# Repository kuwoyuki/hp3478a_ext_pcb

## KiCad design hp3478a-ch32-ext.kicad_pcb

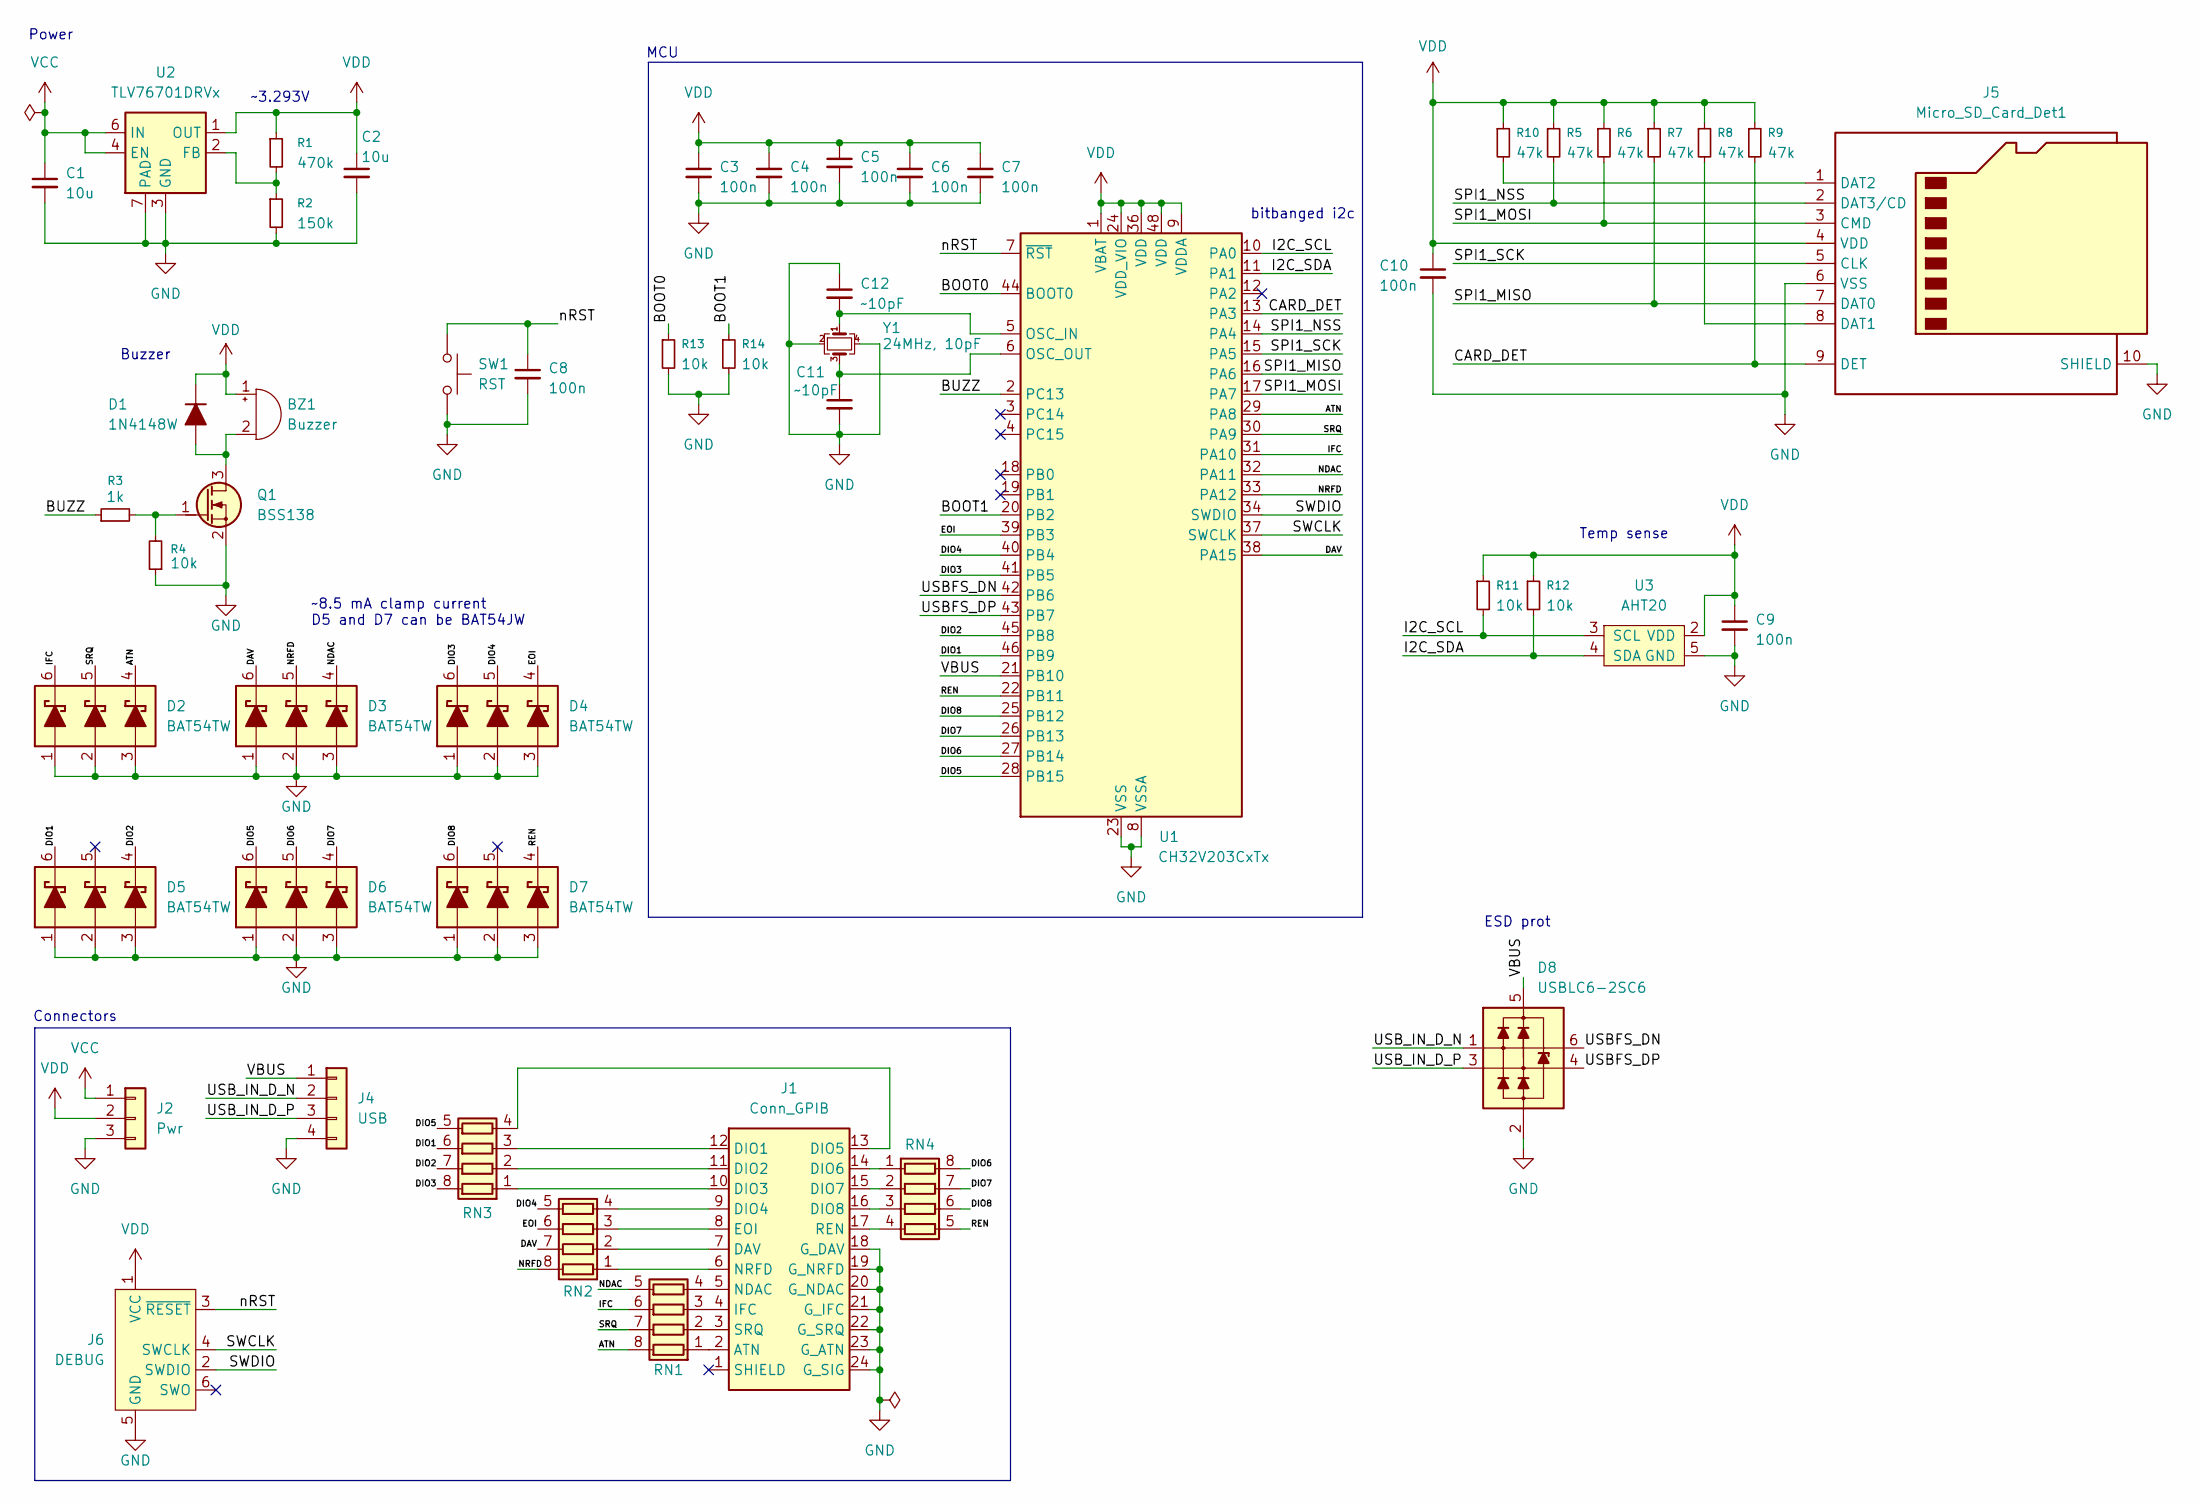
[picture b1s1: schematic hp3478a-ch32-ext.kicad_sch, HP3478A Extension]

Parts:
BZ1: Buzzer; MagneticBuzzer_StarMicronics_QMB-105
C1: 10u; C_1206_3216Metric
C2: 10u; C_0805_2012Metric
C3, C4, C5, C6, C7, C8, C9, C10: 100n; C_0402_1005Metric
C11, C12: ~10pF; C_0402_1005Metric
D1: 1N4148W; D_SOD-323
D2, D3, D4, D5, D6, D7: BAT54TW; SOT-363_SC-70-6
D8: USBLC6-2SC6; SOT-23-6
J1: Conn_GPIB; DIP-24_18.0mmx34.29mm_W15.24mm_Socket
J2: Pwr; SolderWire-0.127sqmm_1x03_P3.7mm_D0.48mm_OD1mm
J4: USB; Molex_PicoBlade_53047-0410_1x04_P1.25mm_Vertical
J5: Micro_SD_Card_Det1; J_SD_Card-micro_socket_A
J6: DEBUG; Tag-Connect_TC2030-IDC-NL_2x03_P1.27mm_Vertical
Q1: BSS138; SOT-23
R1: 470k; R_0603_1608Metric
R2: 150k; R_0603_1608Metric
R3: 1k; R_0603_1608Metric
R4: 10k; R_0603_1608Metric
R5, R6, R7, R8, R9, R10: 47k; R_0402_1005Metric
R11, R12, R13, R14: 10k; R_0402_1005Metric
RN1, RN2, RN3, RN4: R_Pack04; R_Array_Convex_4x0603
SW1: RST; SW_SPST_PTS810
U1: CH32V203CxTx; LQFP-48_7x7mm_P0.5mm
U2: TLV76701DRVx; WSON-6-1EP_2x2mm_P0.65mm_EP1x1.6mm_ThermalVias
U3: AHT20
Y1: 24MHz, 10pF; Crystal_SMD_3225-4Pin_3.2x2.5mm

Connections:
/ATN: D2.4 (K3), RN1.8 (R1.2), U1.29 (PA8)
/BOOT0: R13.1, U1.44 (BOOT0)
/BOOT1: R14.1, U1.20 (PB2)
/BUZZ: R3.1, U1.2 (PC13)
/CARD_DET: J5.9 (DET), R9.2, U1.13 (PA3)
/DAV: D3.6 (K1), RN2.7 (R2.2), U1.38 (PA15)
/DIO1: D5.6 (K1), RN3.6 (R3.2), U1.46 (PB9)
/DIO2: D5.4 (K3), RN3.7 (R2.2), U1.45 (PB8)
/DIO3: D4.6 (K1), RN3.8 (R1.2), U1.41 (PB5)
/DIO4: D4.5 (K2), RN2.5 (R4.2), U1.40 (PB4)
/DIO5: D6.6 (K1), RN3.5 (R4.2), U1.28 (PB15)
/DIO6: D6.5 (K2), RN4.8 (R1.2), U1.27 (PB14)
/DIO7: D6.4 (K3), RN4.7 (R2.2), U1.26 (PB13)
/DIO8: D7.6 (K1), RN4.6 (R3.2), U1.25 (PB12)
/EOI: D4.4 (K3), RN2.6 (R3.2), U1.39 (PB3)
/I2C_SCL: R11.2, U1.10 (PA0), U3.3 (SCL)
/I2C_SDA: R12.2, U1.11 (PA1), U3.4 (SDA)
/IFC: D2.6 (K1), RN1.6 (R3.2), U1.31 (PA10)
/NDAC: D3.4 (K3), RN1.5 (R4.2), U1.32 (PA11)
/NRFD: D3.5 (K2), RN2.8 (R1.2), U1.33 (PA12)
/REN: D7.4 (K3), RN4.5 (R4.2), U1.22 (PB11)
/SPI1_MISO: J5.7 (DAT0), R7.2, U1.16 (PA6)
/SPI1_MOSI: J5.3 (CMD), R6.2, U1.17 (PA7)
/SPI1_NSS: J5.2 (DAT3/CD), R5.2, U1.14 (PA4)
/SPI1_SCK: J5.5 (CLK), U1.15 (PA5)
/SRQ: D2.5 (K2), RN1.7 (R2.2), U1.30 (PA9)
/SWCLK: J6.4 (SWCLK), U1.37 (SWCLK); also elsewhere on the board
/SWDIO: J6.2 (SWDIO), U1.34 (SWDIO); also elsewhere on the board
/USBFS_DN: D8.6 (L1), U1.42 (PB6)
/USBFS_DP: D8.4 (L2), U1.43 (PB7)
/USB_IN_D_N: D8.1 (L1), J4.2
/USB_IN_D_P: D8.3 (L2), J4.3
/VBUS: D8.5 (VP), J4.1, U1.21 (PB10)
/nRST: C8.1, J6.3 (~RESET), SW1.1, U1.7 (~RST); also elsewhere on the board
GND: C1.2, C2.2, C3.2, C4.2, C5.2, C6.2, C7.2, C8.2, C9.2, C10.2, C11.2, C12.1, D2.1 (A1), D2.2 (A2), D2.3 (A3), D3.1 (A1), D3.2 (A2), D3.3 (A3), D4.1 (A1), D4.2 (A2), D4.3 (A3), D5.1 (A1), D5.2 (A2), D5.3 (A3), D6.1 (A1), D6.2 (A2), D6.3 (A3), D7.1 (A1), D7.2 (A2), D7.3 (A3), D8.2 (VN), J1.18 (G_DAV), J1.19 (G_NRFD), J1.20 (G_NDAC), J1.21 (G_IFC), J1.22 (G_SRQ), J1.23 (G_ATN), J1.24 (G_SIG), J2.3, J4.4, J5.6 (VSS), J5.10 (SHIELD), J6.5 (GND), Q1.2 (S), R2.2, R4.1, R13.2, R14.2, SW1.2, U1.8 (VSSA), U1.23 (VSS), U1.35 (VSS), U1.47 (VSS), U2.3 (GND), U2.5 (GND), U2.7 (PAD), U3.5 (GND), Y1.2, Y1.4; also elsewhere on the board
unnamed: BZ1.2 (-), D1.2 (A), Q1.3 (D)
unnamed: J1.2 (ATN), RN1.1 (R1.1)
unnamed: J1.7 (DAV), RN2.2 (R2.1)
unnamed: J1.12 (DIO1), RN3.3 (R3.1)
unnamed: J1.11 (DIO2), RN3.2 (R2.1)
unnamed: J1.10 (DIO3), RN3.1 (R1.1)
unnamed: J1.9 (DIO4), RN2.4 (R4.1)
unnamed: J1.13 (DIO5), RN3.4 (R4.1)
unnamed: J1.14 (DIO6), RN4.1 (R1.1)
unnamed: J1.15 (DIO7), RN4.2 (R2.1)
unnamed: J1.16 (DIO8), RN4.3 (R3.1)
unnamed: J1.8 (EOI), RN2.3 (R3.1)
unnamed: J1.4 (IFC), RN1.3 (R3.1)
unnamed: J1.5 (NDAC), RN1.4 (R4.1)
unnamed: J1.6 (NRFD), RN2.1 (R1.1)
unnamed: J1.17 (REN), RN4.4 (R4.1)
unnamed: J1.3 (SRQ), RN1.2 (R2.1)
unnamed: J5.8 (DAT1), R8.2
unnamed: J5.1 (DAT2), R10.2
unnamed: Q1.1 (G), R3.2, R4.2
unnamed: C12.2, U1.5 (OSC_IN), Y1.1
unnamed: C11.1, U1.6 (OSC_OUT), Y1.3
unnamed: R1.2, R2.1, U2.2 (FB)
VCC: C1.1, J2.1, U2.4 (EN), U2.6 (IN)
VDD: BZ1.1 (+), C2.1, C3.1, C4.1, C5.1, C6.1, C7.1, C9.1, C10.1, D1.1 (K), J2.2, J5.4 (VDD), J6.1 (VCC), R1.1, R5.1, R6.1, R7.1, R8.1, R9.1, R10.1, R11.1, R12.1, U1.1 (VBAT), U1.9 (VDDA), U1.24 (VDD_VIO), U1.36 (VDD), U1.48 (VDD), U2.1 (OUT), U3.2 (VDD); also elsewhere on the board

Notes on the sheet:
Buzzer
~3.293V
ESD prot
Power
bitbanged i2c
~8.5 mA clamp current D5 and D7 can be BAT54JW
Temp sense
Connectors
MCU

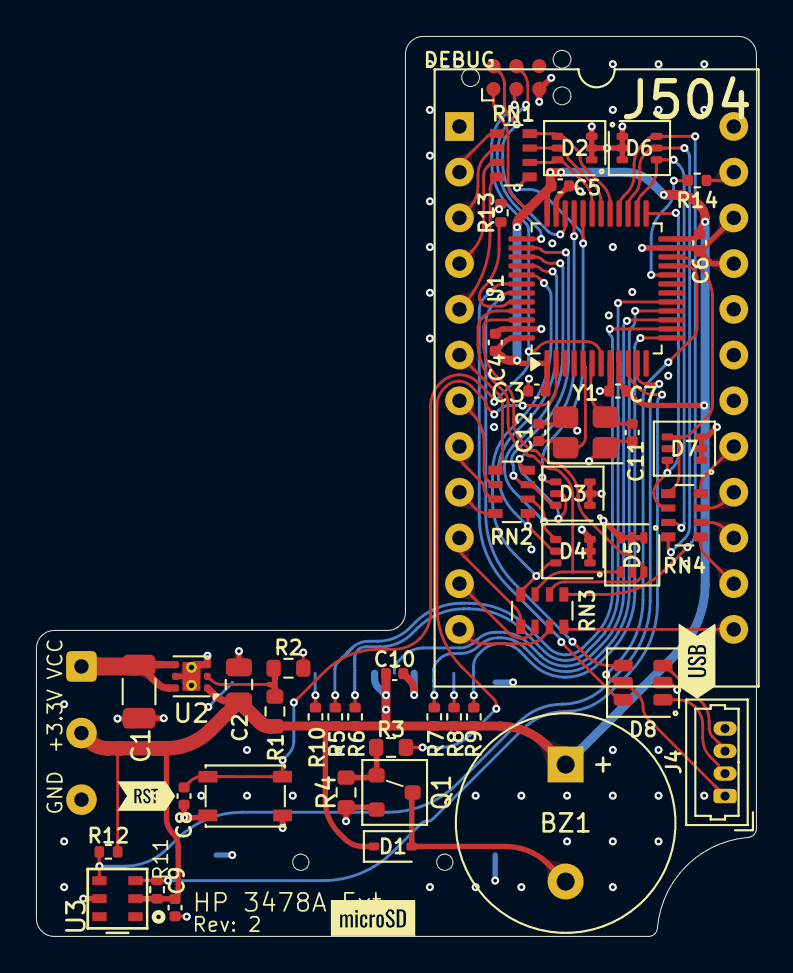
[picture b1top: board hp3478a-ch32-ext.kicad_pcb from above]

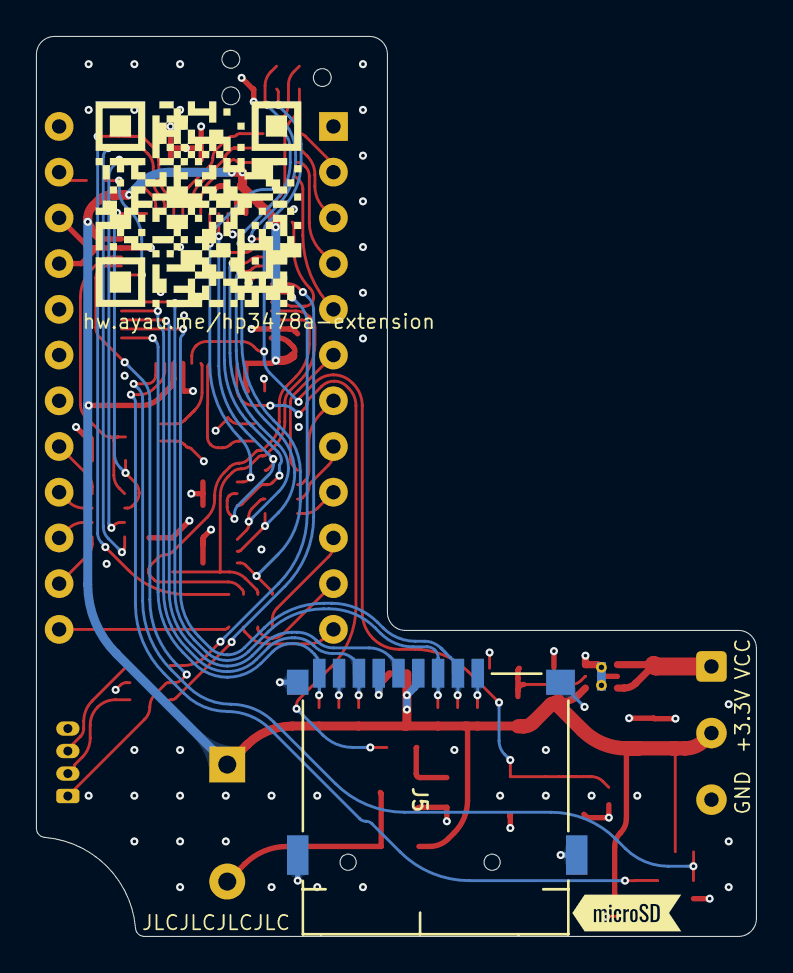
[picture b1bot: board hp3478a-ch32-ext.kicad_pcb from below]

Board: 4 copper layers, 40.0 x 50.0 mm, 54 parts (2 on the bottom side), 60 nets.

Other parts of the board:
DEBUG: DEBUG; Tag-Connect_TC2030-IDC-NL_2x03_P1.27mm_Vertical
kibuzzard-68A1C101: G***; kibuzzard-68A1C101
kibuzzard-68A1C131: G***; kibuzzard-68A1C131
kibuzzard-68A1C183: G***; kibuzzard-68A1C183
kibuzzard-68A1C999: G***; kibuzzard-68A1C999

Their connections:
/SWCLK: DEBUG.4 (SWCLK); also elsewhere on the board
/SWDIO: DEBUG.2 (SWDIO); also elsewhere on the board
/nRST: DEBUG.3 (~RESET); also elsewhere on the board
GND: DEBUG.5 (GND); also elsewhere on the board
VDD: DEBUG.1 (VCC); also elsewhere on the board

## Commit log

2025-08-15 chore: _
2025-08-17 chore: -
2025-08-17 fix: _
2025-08-17 chore: rm
2025-08-17 chore: upd
2025-08-17 fix: hole clearance
